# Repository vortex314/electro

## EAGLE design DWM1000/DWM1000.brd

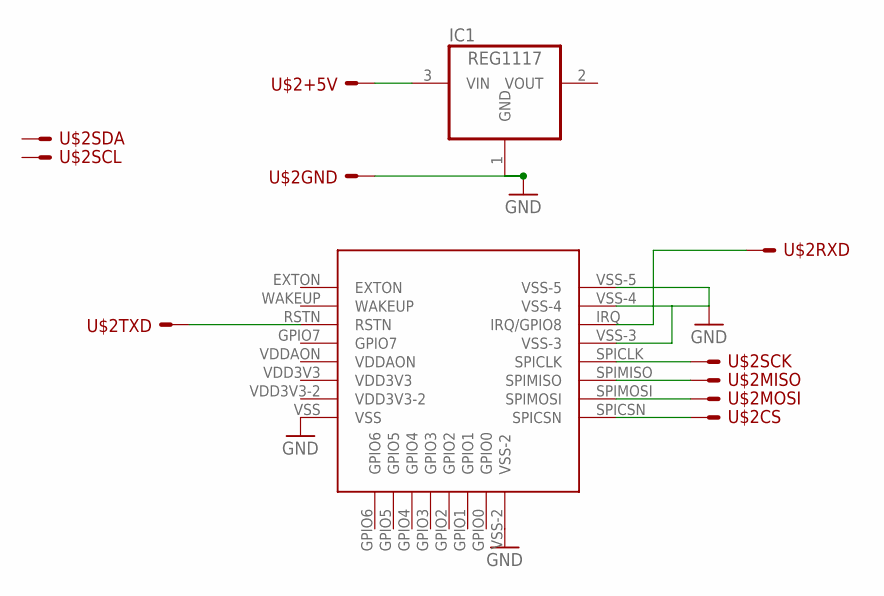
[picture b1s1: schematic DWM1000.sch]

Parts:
IC1: REG1117; SOT223
U$1: DWM1000
U$2: SPI_BUS

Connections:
GND: IC1.1 (GND), U$1.VSS, U$1.VSS-2, U$1.VSS-3, U$1.VSS-4, U$1.VSS-5, U$2.GND
unnamed: IC1.3 (VIN), U$2.+5V
unnamed: U$1.SPICLK, U$2.SCK
unnamed: U$1.SPIMISO, U$2.MISO
unnamed: U$1.SPIMOSI, U$2.MOSI
unnamed: U$1.RSTN, U$2.TXD
unnamed: U$1.IRQ (IRQ/GPIO8), U$2.RXD

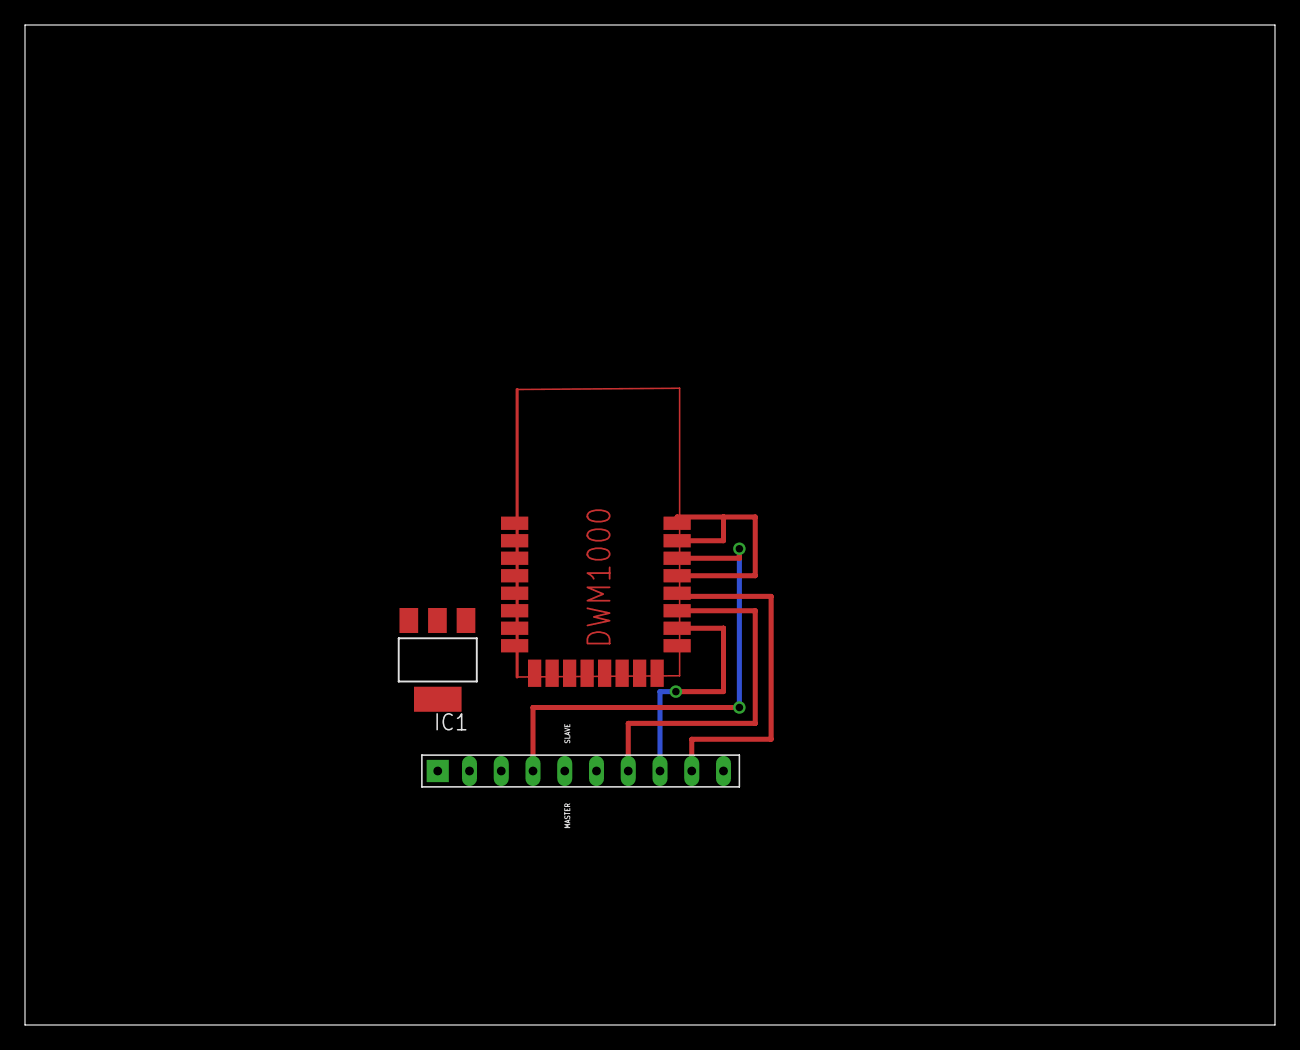
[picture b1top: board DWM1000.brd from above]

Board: 2 copper layers, 100.0 x 80.0 mm, 3 parts (0 on the bottom side), 7 nets.

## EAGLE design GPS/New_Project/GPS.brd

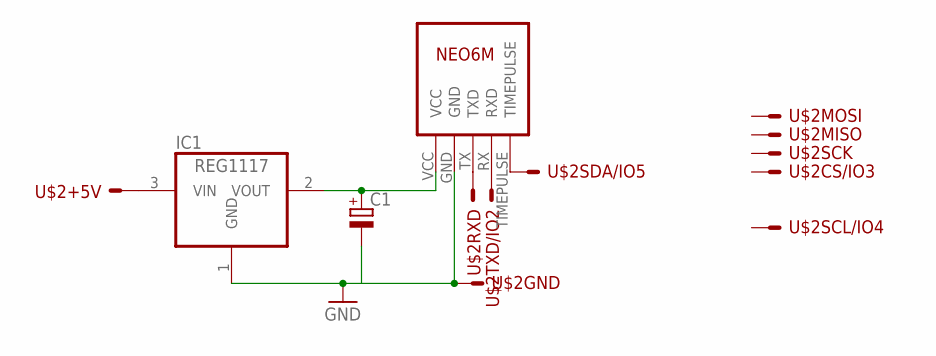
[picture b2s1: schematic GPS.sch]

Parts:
C1: CPOL-EUB45181A; B45181A
IC1: REG1117; SOT223
U$1: NEO6M
U$2: LIMERO_BUS; SPI_BUS

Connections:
GND: C1.-, IC1.1 (GND), U$1.GND, U$2.GND
unnamed: C1.+, IC1.2 (VOUT), U$1.VCC
unnamed: U$1.TX (TXD), U$2.RXD
unnamed: U$1.RX (RXD), U$2.TXD
unnamed: U$1.TIMEPULSE, U$2.SDA
unnamed: IC1.3 (VIN), U$2.+5V

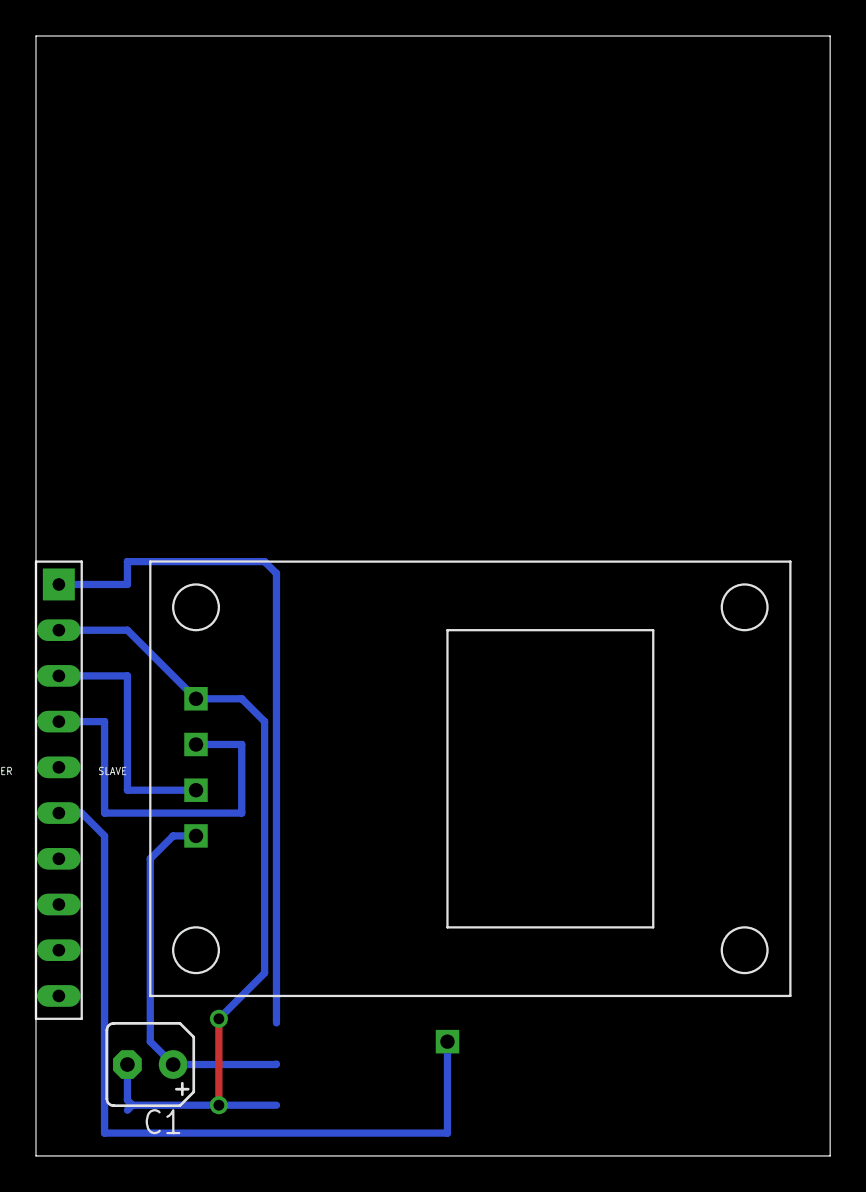
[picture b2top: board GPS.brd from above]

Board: 2 copper layers, 44.1 x 62.2 mm, 4 parts (1 on the bottom side), 6 nets.

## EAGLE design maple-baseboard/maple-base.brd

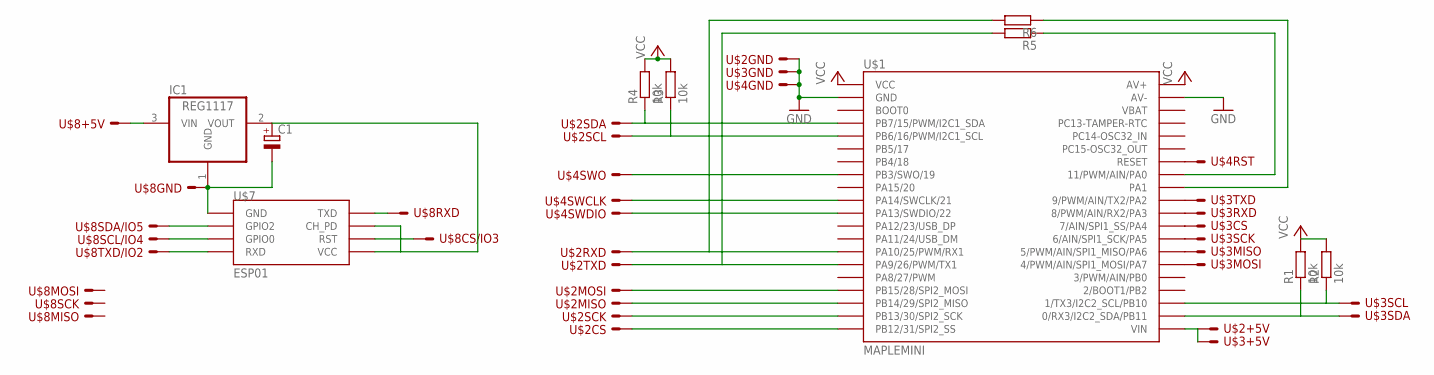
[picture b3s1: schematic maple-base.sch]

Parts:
C1: CPOL-EUB45181A; B45181A
IC1: REG1117; SOT223
R1, R2, R3, R4: 10k; 0207/7
R5, R6: R-EU_0207/7; 0207/7
U$1: MAPLEMINI; 20-DIP
U$2, U$3: SPI_BUS
U$4: SWD
U$7: ESP01
U$8: LIMERO_BUS; SPI_BUS

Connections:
GND: U$1.2 (GND), U$1.39 (AV-), U$2.GND, U$3.GND, U$4.GND
unnamed: U$1.11 (PA13/SWDIO/22), U$4.SWDIO
unnamed: U$1.10 (PA14/SWCLK/21), U$4.SWCLK
unnamed: U$1.34 (RESET), U$4.RST
unnamed: R5.1, U$1.33 (11/PWM/AIN/PA0)
unnamed: R6.2, U$1.14 (PA10/25/PWM/RX1), U$2.RXD
unnamed: R5.2, U$1.15 (PA9/26/PWM/TX1), U$2.TXD
unnamed: U$1.18 (PB14/29/SPI2_MISO), U$2.MISO
unnamed: U$1.17 (PB15/28/SPI2_MOSI), U$2.MOSI
unnamed: U$1.19 (PB13/30/SPI2_SCK), U$2.SCK
unnamed: U$1.20 (PB12/31/SPI2_SS), U$2.CS
unnamed: R4.1, U$1.4 (PB7/15/PWM/I2C1_SDA), U$2.SDA
unnamed: R3.1, U$1.5 (PB6/16/PWM/I2C1_SCL), U$2.SCL
unnamed: U$1.30 (8/PWM/AIN/RX2/PA3), U$3.RXD
unnamed: U$1.31 (9/PWM/AIN/TX2/PA2), U$3.TXD
unnamed: U$1.29 (7/AIN/SPI1_SS/PA4), U$3.CS
unnamed: U$1.28 (6/AIN/SPI1_SCK/PA5), U$3.SCK
unnamed: U$1.27 (5/PWM/AIN/SPI1_MISO/PA6), U$3.MISO
unnamed: U$1.26 (4/PWM/AIN/SPI1_MOSI/PA7), U$3.MOSI
unnamed: R2.1, U$1.23 (1/TX3/I2C2_SCL/PB10), U$3.SCL
unnamed: R1.1, U$1.22 (0/RX3/I2C2_SDA/PB11), U$3.SDA
unnamed: U$1.21 (VIN), U$2.+5V, U$3.+5V
unnamed: U$1.8 (PB3/SWO/19), U$4.SWO
unnamed: R6.1, U$1.32 (PA1)
unnamed: C1.-, IC1.1 (GND), U$7.GND, U$8.GND
unnamed: U$7.RX (RXD), U$8.TXD
unnamed: U$7.TX (TXD), U$8.RXD
unnamed: U$7.RST, U$8.CS
unnamed: IC1.3 (VIN), U$8.+5V
unnamed: C1.+, IC1.2 (VOUT), U$7.CH_PD, U$7.VCC
unnamed: U$7.GPIO0, U$8.SCL
unnamed: U$7.GPIO2, U$8.SDA
VCC: R1.2, R2.2, R3.2, R4.2, U$1.1 (VCC), U$1.40 (AV+)

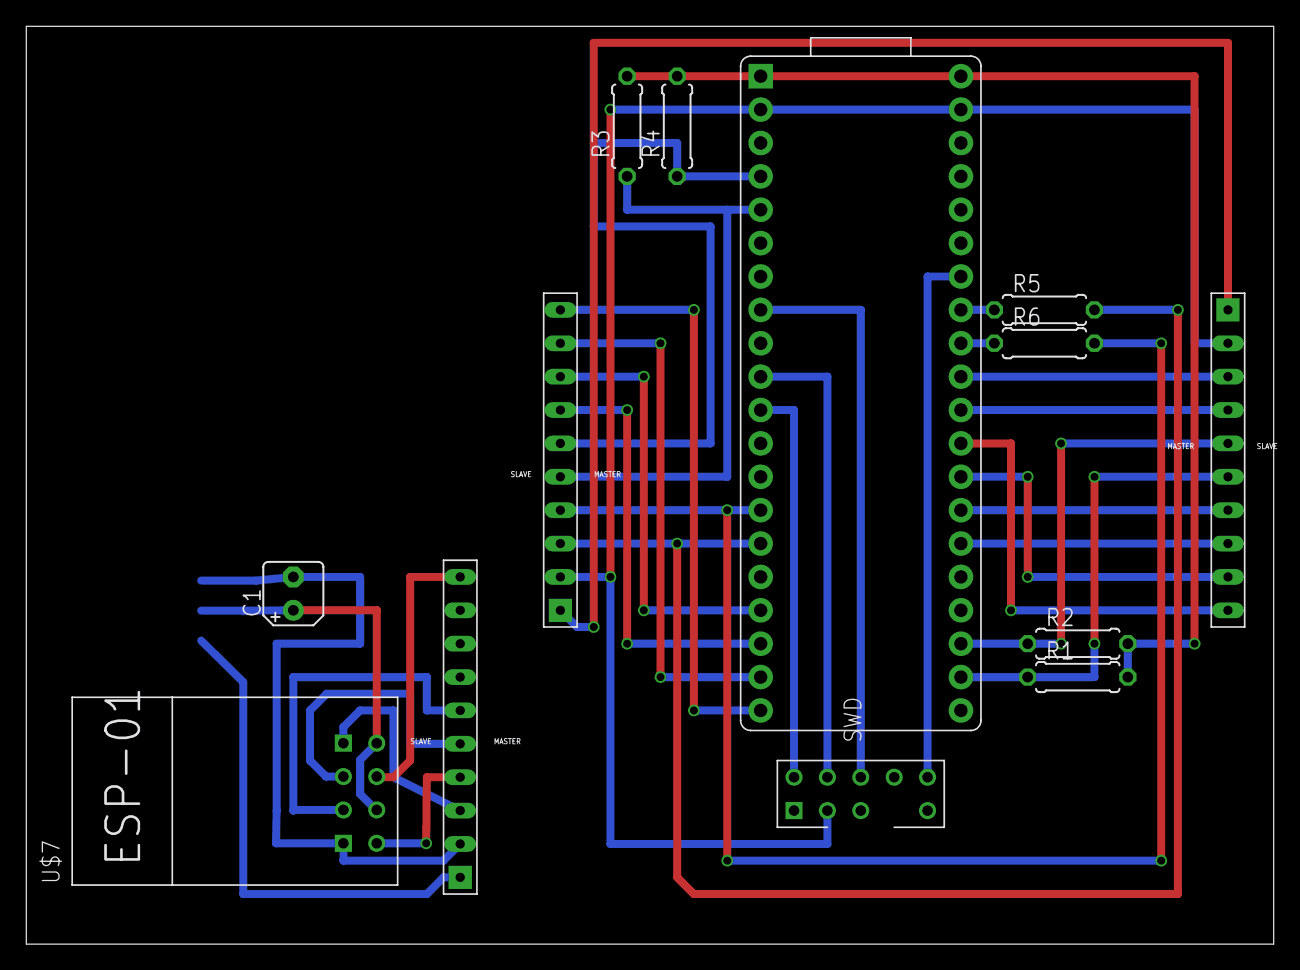
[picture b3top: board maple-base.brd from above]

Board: 2 copper layers, 94.9 x 69.8 mm, 14 parts (1 on the bottom side), 33 nets.

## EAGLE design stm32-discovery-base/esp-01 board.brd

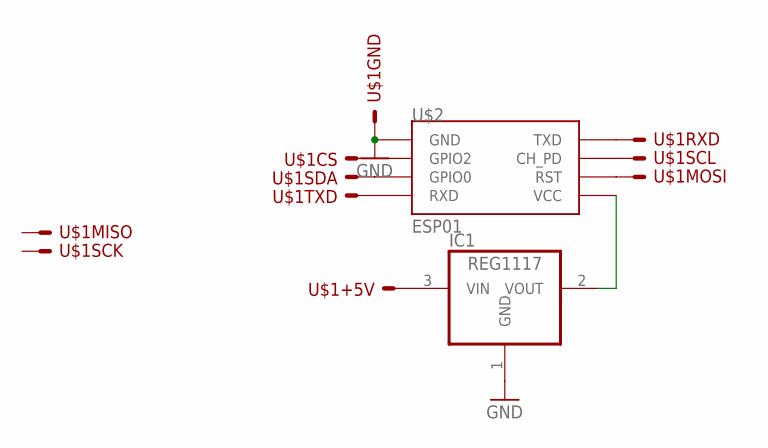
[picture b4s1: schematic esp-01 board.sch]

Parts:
IC1: REG1117; SOT223
U$1: SPI_BUS
U$2: ESP01

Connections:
GND: IC1.1 (GND), U$1.GND, U$2.GND
unnamed: U$1.RXD, U$2.TX (TXD)
unnamed: U$1.TXD, U$2.RX (RXD)
unnamed: U$1.CS, U$2.GPIO2
unnamed: U$1.SDA, U$2.GPIO0
unnamed: U$1.SCL, U$2.CH_PD
unnamed: U$1.MOSI, U$2.RST
unnamed: IC1.3 (VIN), U$1.+5V
unnamed: IC1.2 (VOUT), U$2.VCC

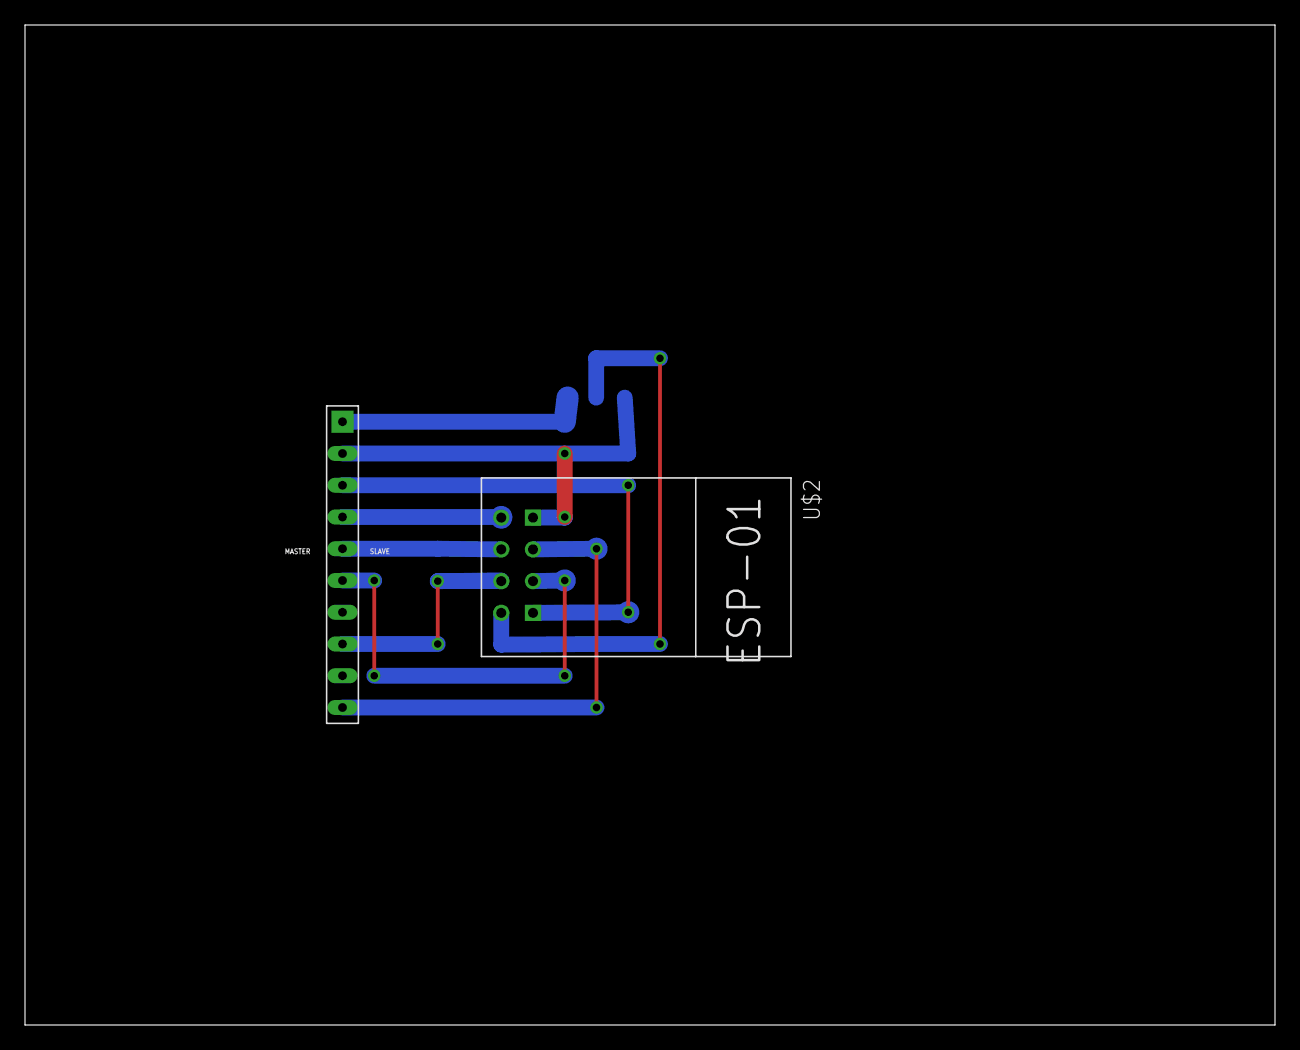
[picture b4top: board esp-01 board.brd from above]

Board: 2 copper layers, 100.0 x 80.0 mm, 3 parts (1 on the bottom side), 9 nets.

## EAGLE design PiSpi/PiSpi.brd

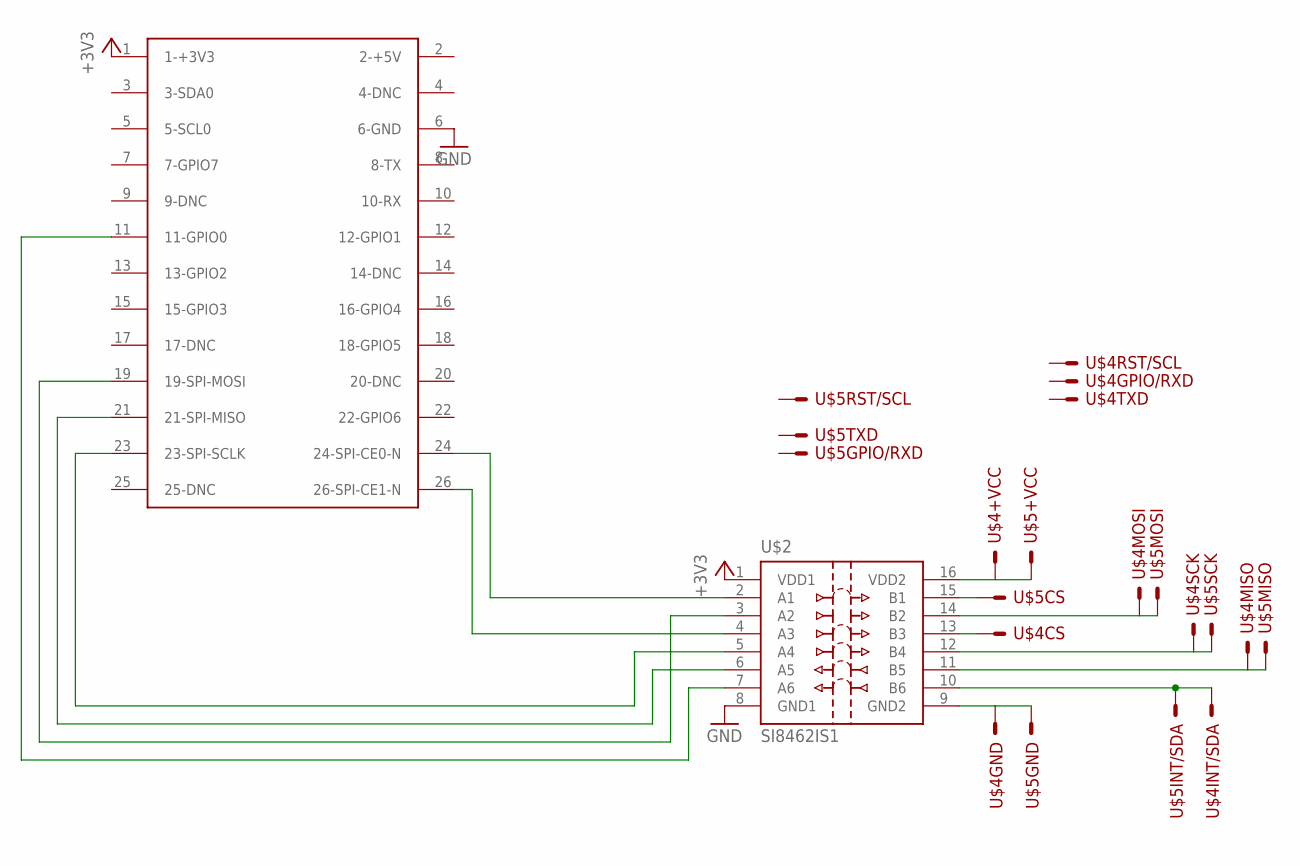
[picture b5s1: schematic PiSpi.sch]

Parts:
U$1: RASPBERRY-PI
U$2: SI8462IS1; SO16
U$4, U$5: SPI_BUS2

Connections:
+3V3: U$1.1 (1-+3V3), U$2.1 (VDD1)
GND: U$1.6 (6-GND), U$2.8 (GND1)
GND1: U$2.9 (GND2), U$4.GND, U$5.GND
unnamed: U$1.24 (24-SPI-CE0-N), U$2.2 (A1)
unnamed: U$2.14 (B2), U$4.MOSI, U$5.MOSI
unnamed: U$2.13 (B3), U$4.CS
unnamed: U$2.12 (B4), U$4.SCK, U$5.SCK
unnamed: U$2.11 (B5), U$4.MISO, U$5.MISO
unnamed: U$2.15 (B1), U$5.CS
unnamed: U$1.11 (11-GPIO0), U$2.7 (A6)
unnamed: U$2.10 (B6), U$4.INT/SDA, U$5.INT/SDA
unnamed: U$1.26 (26-SPI-CE1-N), U$2.4 (A3)
unnamed: U$1.23 (23-SPI-SCLK), U$2.5 (A4)
unnamed: U$1.21 (21-SPI-MISO), U$2.6 (A5)
unnamed: U$1.19 (19-SPI-MOSI), U$2.3 (A2)
unnamed: U$2.16 (VDD2), U$4.+VCC, U$5.+VCC

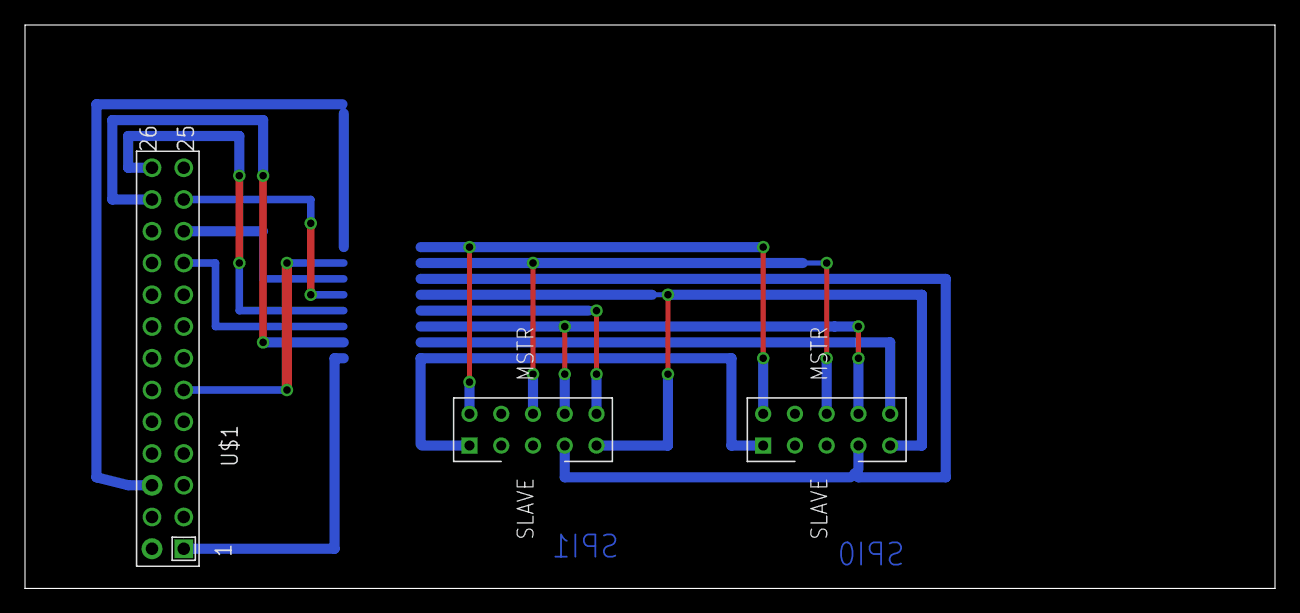
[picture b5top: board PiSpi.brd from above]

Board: 2 copper layers, 100.0 x 45.1 mm, 4 parts (1 on the bottom side), 16 nets.

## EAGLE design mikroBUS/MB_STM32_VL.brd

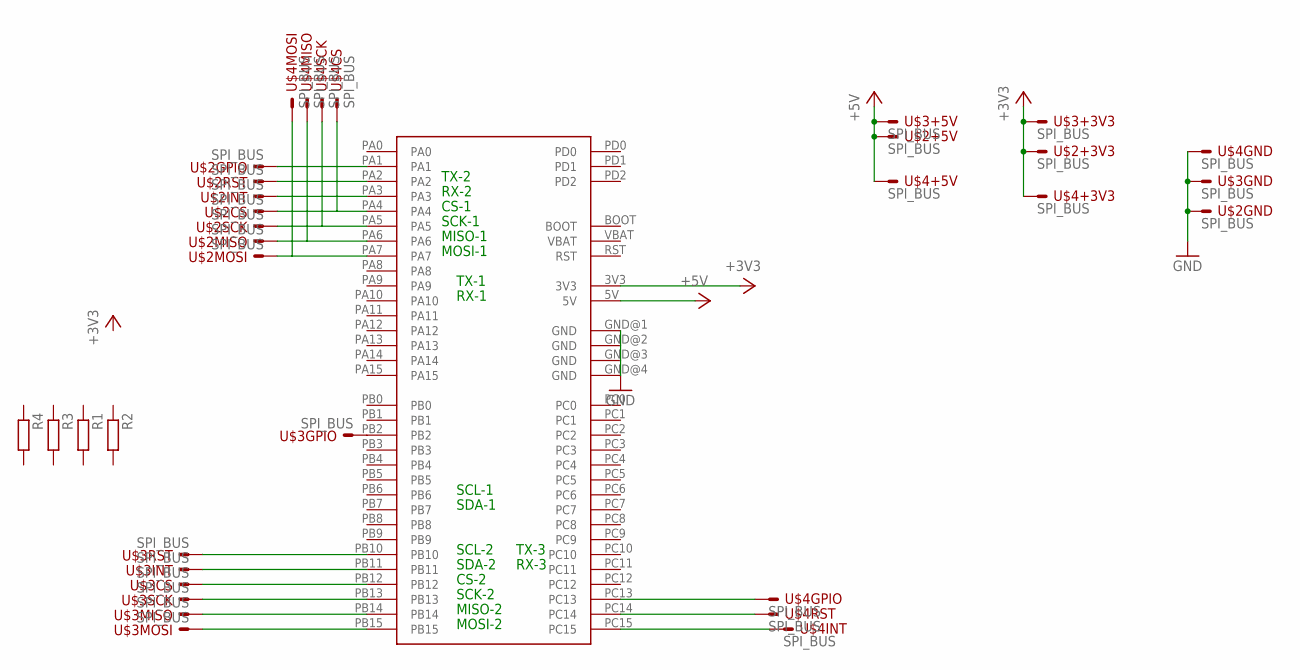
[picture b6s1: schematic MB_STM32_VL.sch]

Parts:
R1, R2, R3, R4: R-EU_0204/7; 0204/7
U$1: STM32_DISCOVERY
U$2, U$3, U$4: SPI_BUS

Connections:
+3V3: U$1.3V3, U$2.+3V3, U$3.+3V3, U$4.+3V3
+5V: U$1.5V, U$2.+5V, U$3.+5V, U$4.+5V
GND: U$1.GND@1 (GND), U$1.GND@2 (GND), U$1.GND@3 (GND), U$1.GND@4 (GND), U$2.GND, U$3.GND, U$4.GND
unnamed: U$1.PA7, U$2.MOSI, U$4.MOSI
unnamed: U$1.PA6, U$2.MISO, U$4.MISO
unnamed: U$1.PA5, U$2.SCK, U$4.SCK
unnamed: U$1.PA4, U$2.CS, U$4.CS
unnamed: U$1.PB15, U$3.MOSI
unnamed: U$1.PB14, U$3.MISO
unnamed: U$1.PB13, U$3.SCK
unnamed: U$1.PB12, U$3.CS
unnamed: U$1.PB11, U$3.INT
unnamed: U$1.PB10, U$3.RST
unnamed: U$1.PB2, U$3.GPIO
unnamed: U$1.PA3, U$2.INT
unnamed: U$1.PA2, U$2.RST
unnamed: U$1.PA1, U$2.GPIO
unnamed: U$1.PC13, U$4.GPIO
unnamed: U$1.PC14, U$4.RST
unnamed: U$1.PC15, U$4.INT

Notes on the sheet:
TX-2
RX-2
CS-1
SCK-1
MISO-1
MOSI-1
SDA-2
SCL-2
TX-1
RX-1
SCL-1
SDA-1
CS-2
SCK-2
MISO-2
MOSI-2
TX-3
RX-3

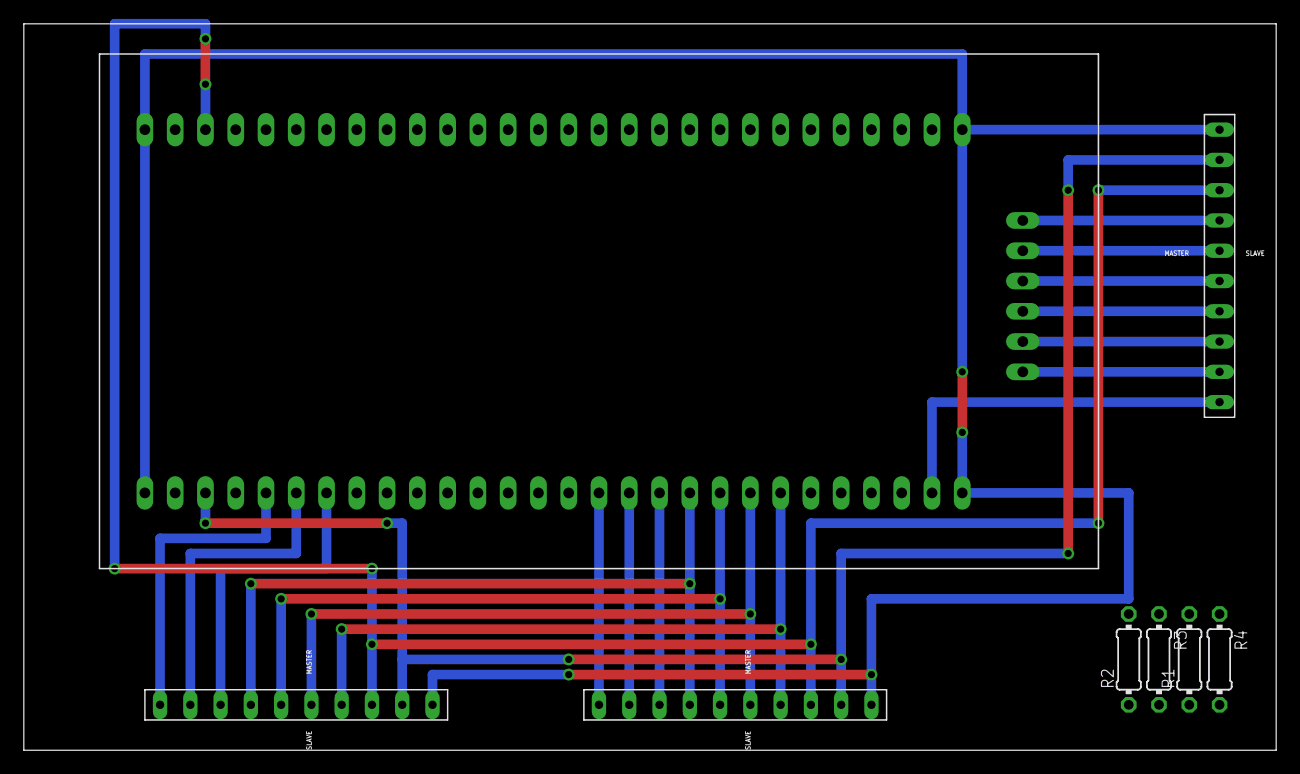
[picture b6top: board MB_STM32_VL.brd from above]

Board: 2 copper layers, 105.1 x 61.0 mm, 8 parts (0 on the bottom side), 20 nets.

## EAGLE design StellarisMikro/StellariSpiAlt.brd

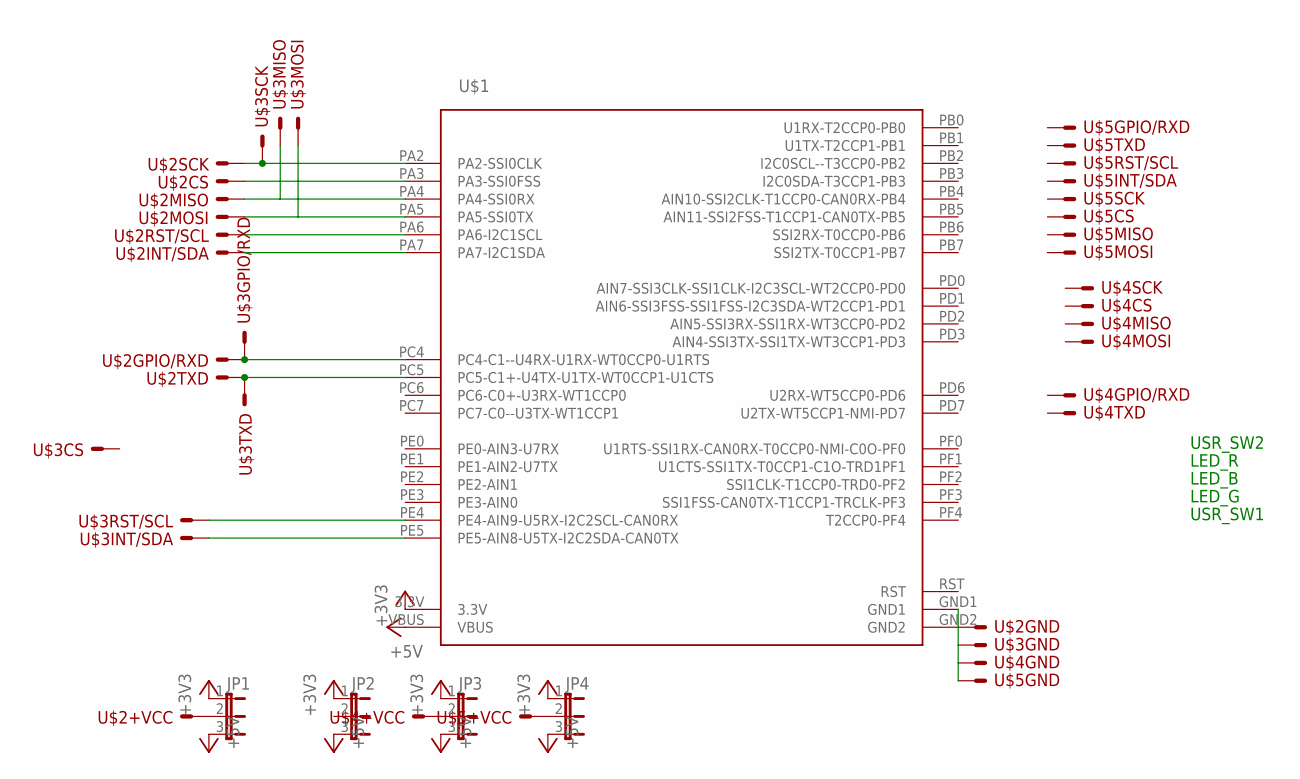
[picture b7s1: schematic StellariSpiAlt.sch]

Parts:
JP1, JP2, JP3, JP4: JP2E; JP2
U$1: STELLARIS-LAUNCHPADSTELLARIS-LAUNCHPAD-XL; LAUNCHPAD-XL
U$2, U$3, U$4, U$5: SPI_BUS2

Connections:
+3V3: JP1.1, JP2.1, JP3.1, JP4.1, U$1.3.3V
+5V: JP1.3, JP2.3, JP3.3, JP4.3, U$1.VBUS
unnamed: U$1.PA2 (PA2-SSI0CLK), U$2.SCK, U$3.SCK
unnamed: U$1.PA4 (PA4-SSI0RX), U$2.MISO, U$3.MISO
unnamed: U$1.PA5 (PA5-SSI0TX), U$2.MOSI, U$3.MOSI
unnamed: U$1.PA3 (PA3-SSI0FSS), U$2.CS
unnamed: U$1.PC5 (PC5-C1+-U4TX-U1TX-WT0CCP1-U1CTS), U$2.TXD, U$3.TXD
unnamed: JP1.2, U$2.+VCC
unnamed: U$1.GND1, U$1.GND2, U$2.GND, U$3.GND, U$4.GND, U$5.GND
unnamed: U$1.PE4 (PE4-AIN9-U5RX-I2C2SCL-CAN0RX), U$3.RST/SCL
unnamed: U$1.PE5 (PE5-AIN8-U5TX-I2C2SDA-CAN0TX), U$3.INT/SDA
unnamed: U$1.PA6 (PA6-I2C1SCL), U$2.RST/SCL
unnamed: U$1.PA7 (PA7-I2C1SDA), U$2.INT/SDA
unnamed: U$1.PC4 (PC4-C1--U4RX-U1RX-WT0CCP0-U1RTS), U$2.GPIO/RXD, U$3.GPIO/RXD
unnamed: JP3.2, U$4.+VCC
unnamed: JP4.2, U$5.+VCC
RST: U$1.RST

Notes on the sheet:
LED_R
LED_B
LED_G
USR_SW2
USR_SW1

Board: 2 copper layers, 9 parts (0 on the bottom side), 16 nets, no tracks yet.

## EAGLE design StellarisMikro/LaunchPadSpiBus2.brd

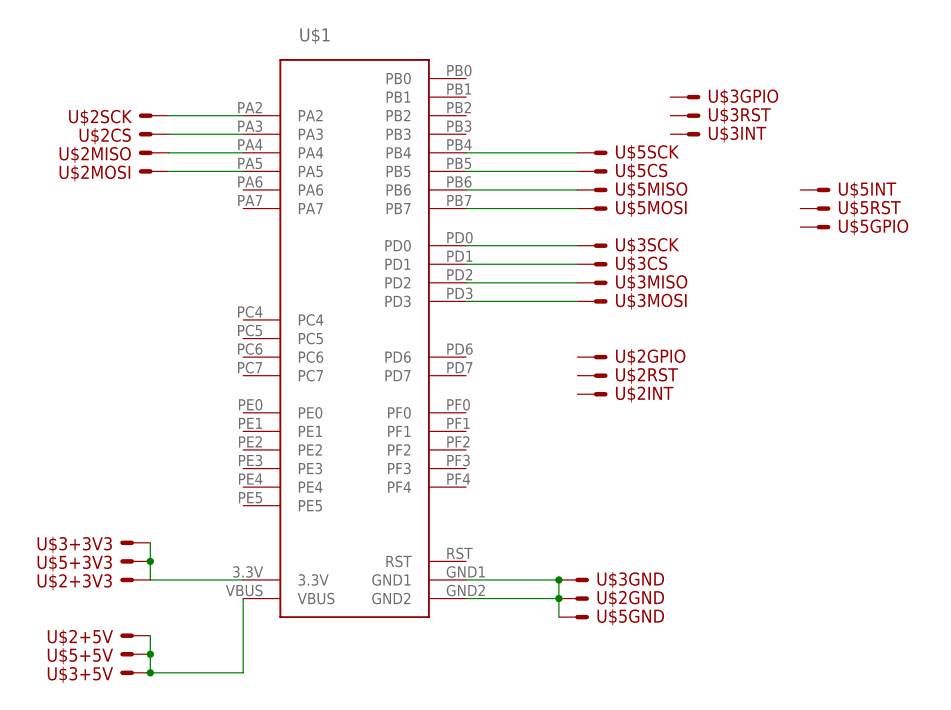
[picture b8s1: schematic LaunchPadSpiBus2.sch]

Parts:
U$1: STELLARIS-LAUNCHPADSTELLARIS-LAUNCHPAD-XL; LAUNCHPAD-XL
U$2, U$3, U$5: SPI_BUS

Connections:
unnamed: U$1.PA3, U$2.CS
unnamed: U$1.PD0, U$3.SCK
unnamed: U$1.PD1, U$3.CS
unnamed: U$1.VBUS, U$2.+5V, U$3.+5V, U$5.+5V
unnamed: U$1.PA2, U$2.SCK
unnamed: U$1.GND1, U$1.GND2, U$2.GND, U$3.GND, U$5.GND
unnamed: U$1.3.3V, U$2.+3V3, U$3.+3V3, U$5.+3V3
unnamed: U$1.PB5, U$5.CS
unnamed: U$1.PA5, U$2.MOSI
unnamed: U$1.PB4, U$5.SCK
unnamed: U$1.PB7, U$5.MOSI
unnamed: U$1.PB6, U$5.MISO
unnamed: U$1.PA4, U$2.MISO
unnamed: U$1.PD2, U$3.MISO
unnamed: U$1.PD3, U$3.MOSI
RST: U$1.RST

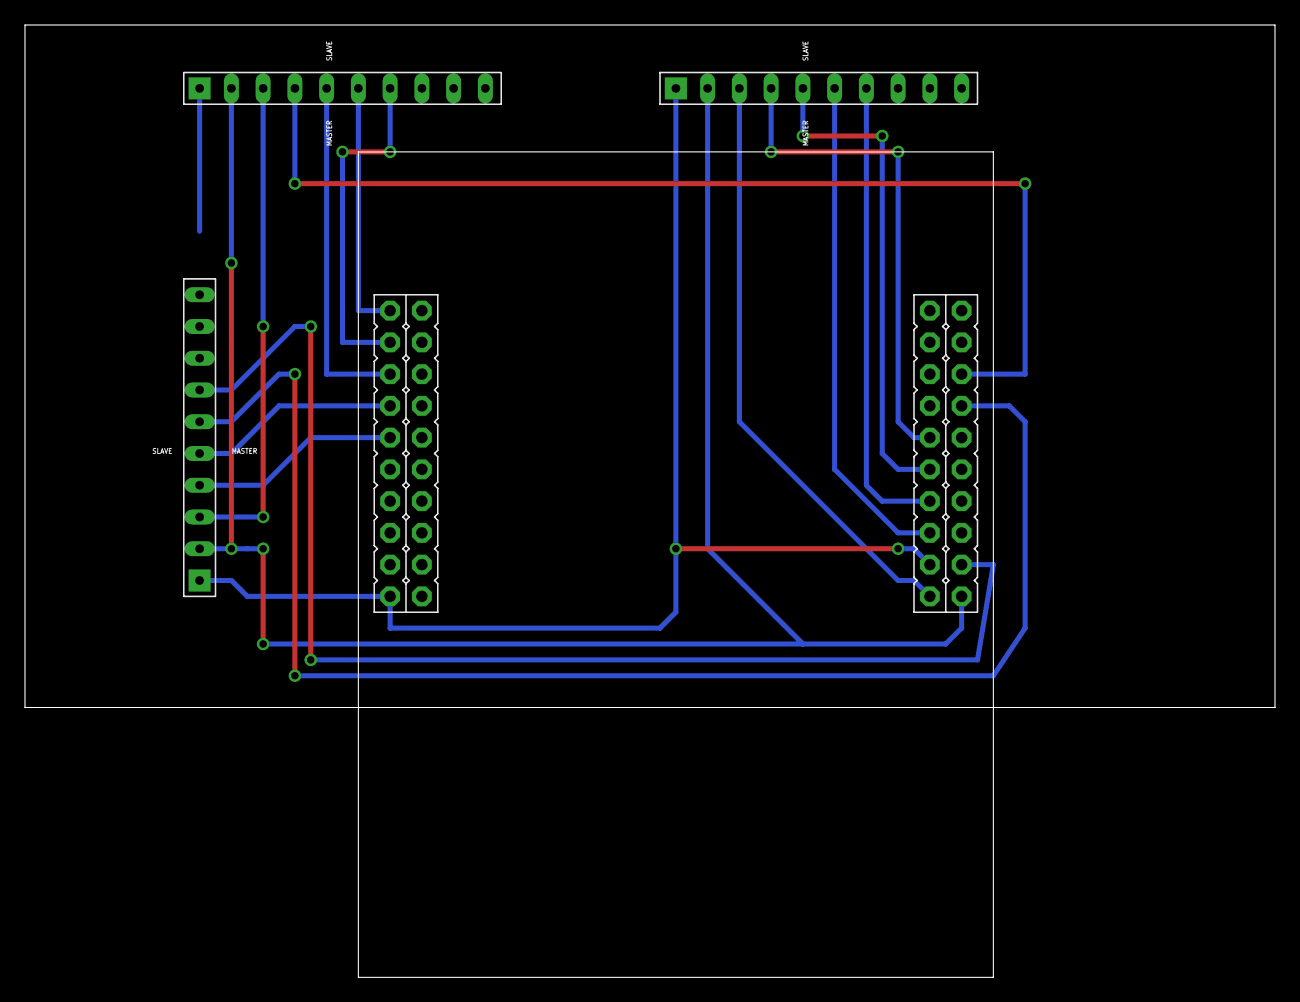
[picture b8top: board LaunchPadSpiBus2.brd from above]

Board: 2 copper layers, 100.0 x 76.2 mm, 4 parts (0 on the bottom side), 15 nets.

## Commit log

2016-01-05 first
2017-12-07 Beacon
2017-12-07 Beacon-Tag
2017-12-07 Beacon Tag
